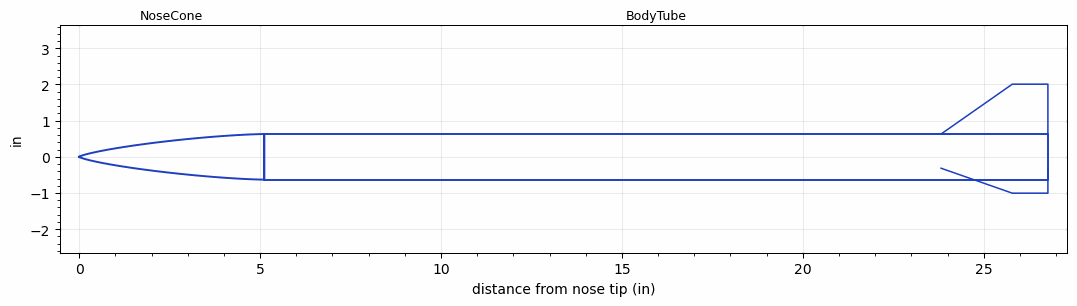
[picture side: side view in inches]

<RASAeroDocument>
 <FileVersion>2</FileVersion>
 <RocketDesign>
  <NoseCone>
   <Length>5.1181102</Length>
   <Diameter>1.2598425</Diameter>
   <Shape>Von Karman Ogive</Shape>
   <Location>0</Location>
  </NoseCone>
  <BodyTube>
   <Length>21.653543</Length>
   <Diameter>1.2598425</Diameter>
   <RailGuideDiameter>0.31496063</RailGuideDiameter>
   <RailGuideHeight>0.31496063</RailGuideHeight>
   <Location>5.1181102</Location>
   <Fin>
    <Count>3</Count>
    <Chord>2.9527559</Chord>
    <Span>1.3779528</Span>
    <SweepDistance>1.9685039</SweepDistance>
    <TipChord>0.98425197</TipChord>
    <Thickness>0.078740157</Thickness>
    <Location>2.9527559</Location>
    <AirfoilSection>Square</AirfoilSection>
   </Fin>
  </BodyTube>
  <Surface>Rough Camouflage Paint</Surface>
  <ModifiedBarrowman>False</ModifiedBarrowman>
  <Turbulence>False</Turbulence>
  <UseBooster1>False</UseBooster1>
  <UseBooster2>False</UseBooster2>
  <Comments>Exported by lo-fi-rocket from "r5-transonic-min-dia-29".</Comments>
 </RocketDesign>
 <LaunchSite>
  <Altitude>0</Altitude>
  <Pressure>0</Pressure>
  <RodAngle>0</RodAngle>
  <RodLength>4.9212598</RodLength>
  <Temperature>59</Temperature>
  <WindSpeed>0</WindSpeed>
 </LaunchSite>
 <Recovery>
  <Altitude1>1000</Altitude1>
  <Altitude2>1000</Altitude2>
  <DeviceType1>Parachute</DeviceType1>
  <DeviceType2>None</DeviceType2>
  <Event1>True</Event1>
  <Event2>False</Event2>
  <Size1>13.779528</Size1>
  <Size2>0</Size2>
  <EventType1>Apogee</EventType1>
  <EventType2>None</EventType2>
  <CD1>0.8</CD1>
  <CD2>1.33</CD2>
 </Recovery>
 <SimulationList>
  <Simulation>
   <SustainerEngine>LF-H238T  (LoFi)</SustainerEngine>
   <SustainerLaunchWt>0.99237888</SustainerLaunchWt>
   <SustainerCG>17.146827</SustainerCG>
   <SustainerIgnitionDelay>0</SustainerIgnitionDelay>
   <Booster1SeparationDelay>0</Booster1SeparationDelay>
   <Booster1IgnitionDelay>0</Booster1IgnitionDelay>
   <IncludeBooster1>False</IncludeBooster1>
   <Booster2Delay>0</Booster2Delay>
   <IncludeBooster2>False</IncludeBooster2>
  </Simulation>
 </SimulationList>
</RASAeroDocument>
